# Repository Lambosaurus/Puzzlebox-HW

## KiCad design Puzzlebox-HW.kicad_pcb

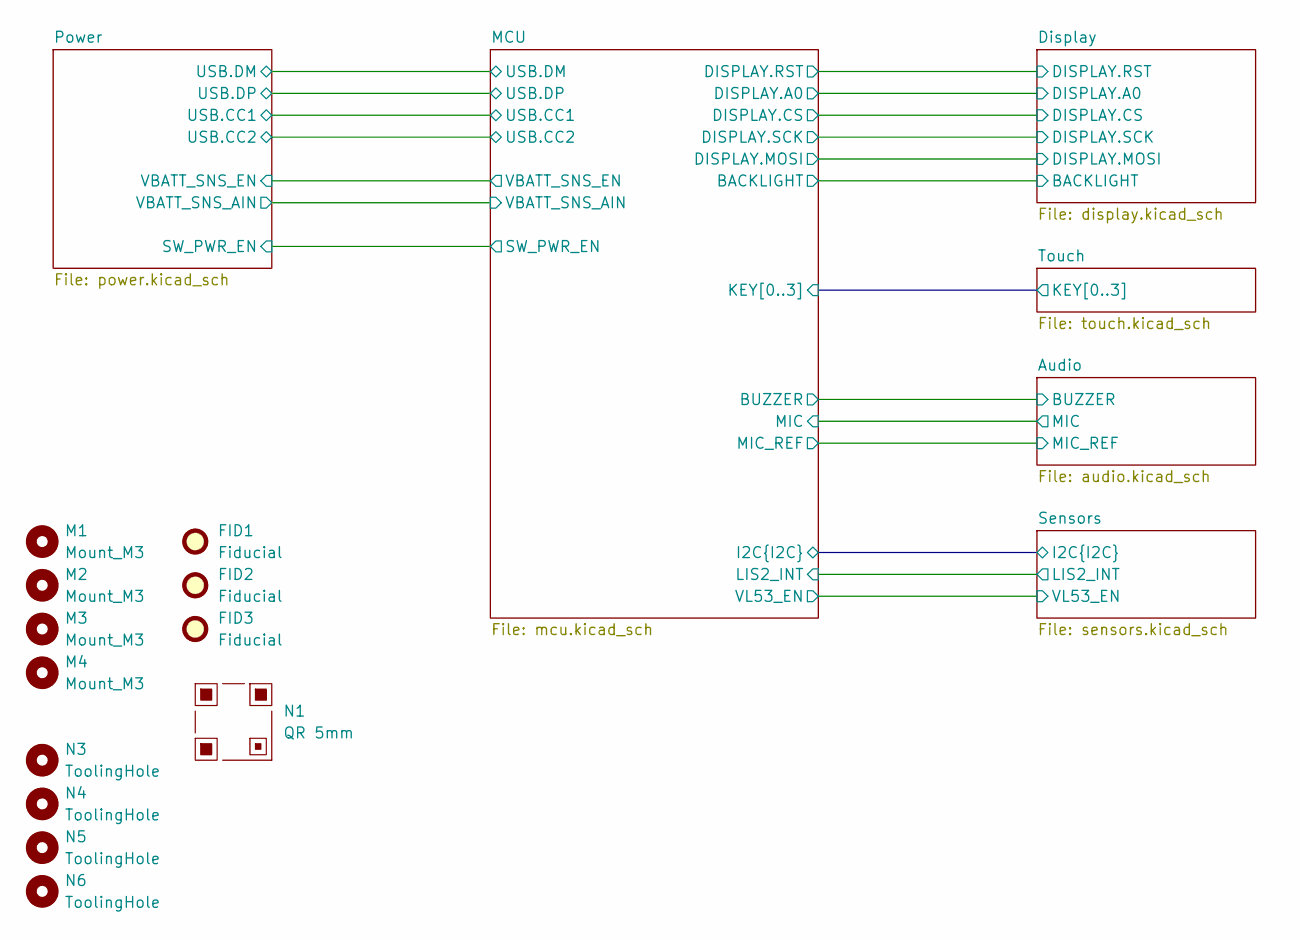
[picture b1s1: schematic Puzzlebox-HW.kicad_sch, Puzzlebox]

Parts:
FID1, FID2, FID3: Fiducial; Fiducial_2mm
M1, M2, M3, M4: Mount_M3
N1: QR 5mm; QR_5mm_JLC
N3, N4, N5, N6: ToolingHole; ToolingHole_1mm

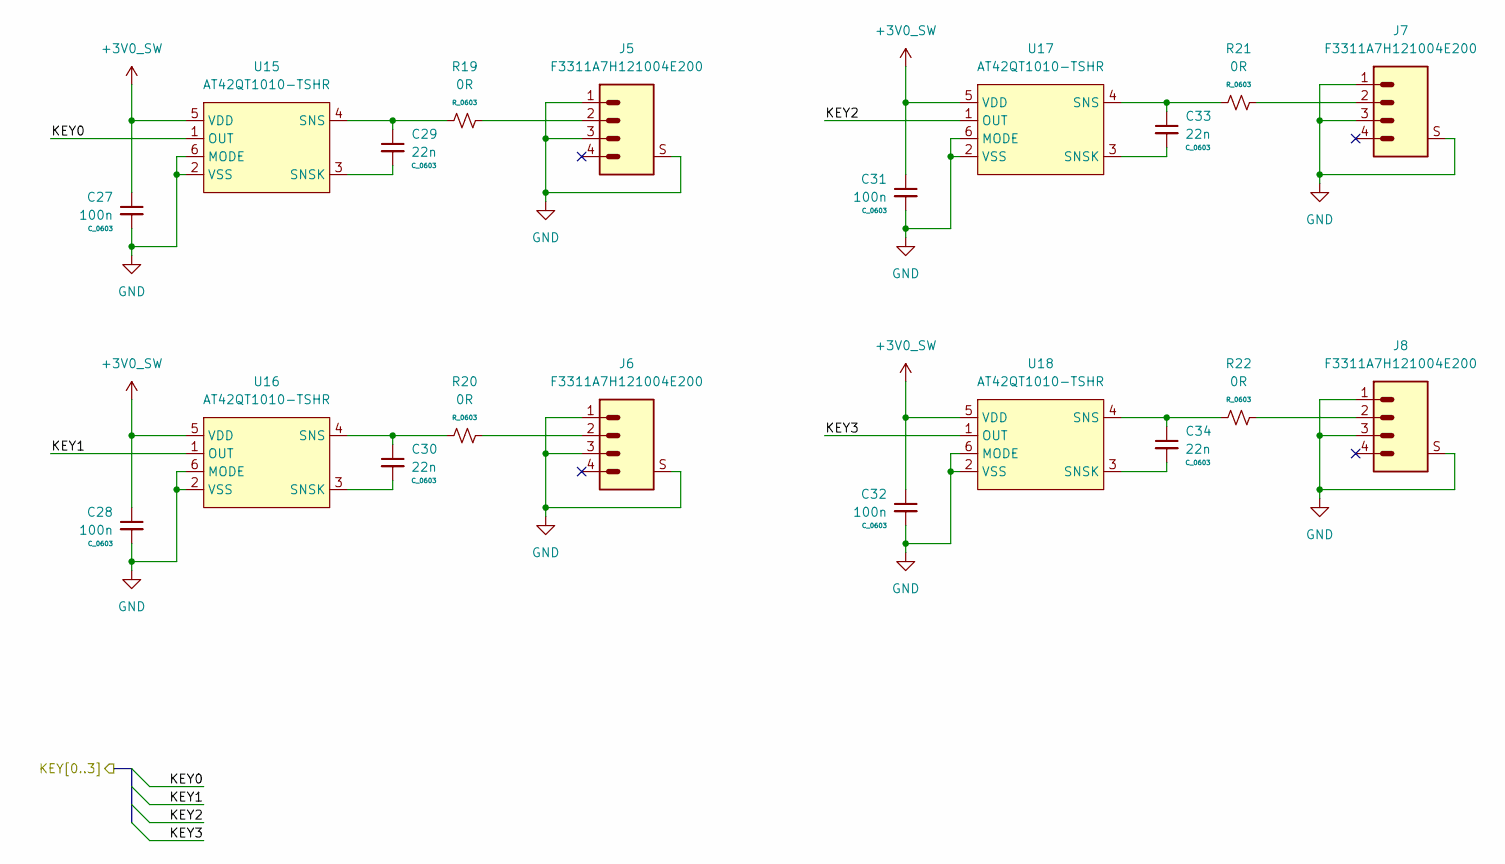
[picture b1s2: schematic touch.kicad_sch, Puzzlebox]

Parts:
C27, C28, C31, C32: 100n; C_0603
C29, C30, C33, C34: 22n; C_0603
J5, J6, J7, J8: F3311A7H121004E200
R19, R20, R21, R22: 0R; R_0603
U15, U16, U17, U18: AT42QT1010-TSHR; SOT23_6

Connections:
+3V0_SW: C27.1, C28.1, C31.1, C32.1, U15.5 (VDD), U16.5 (VDD), U17.5 (VDD), U18.5 (VDD); also elsewhere on the board
/MCU/KEY0: U15.1 (OUT); also elsewhere on the board
/MCU/KEY1: U16.1 (OUT); also elsewhere on the board
/MCU/KEY2: U17.1 (OUT); also elsewhere on the board
/MCU/KEY3: U18.1 (OUT); also elsewhere on the board
GND: C27.2, C28.2, C31.2, C32.2, J5.1, J5.3, J5.S, J6.1, J6.3, J6.S, J7.1, J7.3, J7.S, J8.1, J8.3, J8.S, U15.2 (VSS), U15.6 (MODE), U16.2 (VSS), U16.6 (MODE), U17.2 (VSS), U17.6 (MODE), U18.2 (VSS), U18.6 (MODE); also elsewhere on the board
unnamed: J5.2, R19.2
unnamed: J6.2, R20.2
unnamed: J7.2, R21.2
unnamed: J8.2, R22.2
unnamed: C29.1, R19.1, U15.4 (SNS)
unnamed: C29.2, U15.3 (SNSK)
unnamed: C30.1, R20.1, U16.4 (SNS)
unnamed: C30.2, U16.3 (SNSK)
unnamed: C33.1, R21.1, U17.4 (SNS)
unnamed: C33.2, U17.3 (SNSK)
unnamed: C34.1, R22.1, U18.4 (SNS)
unnamed: C34.2, U18.3 (SNSK)

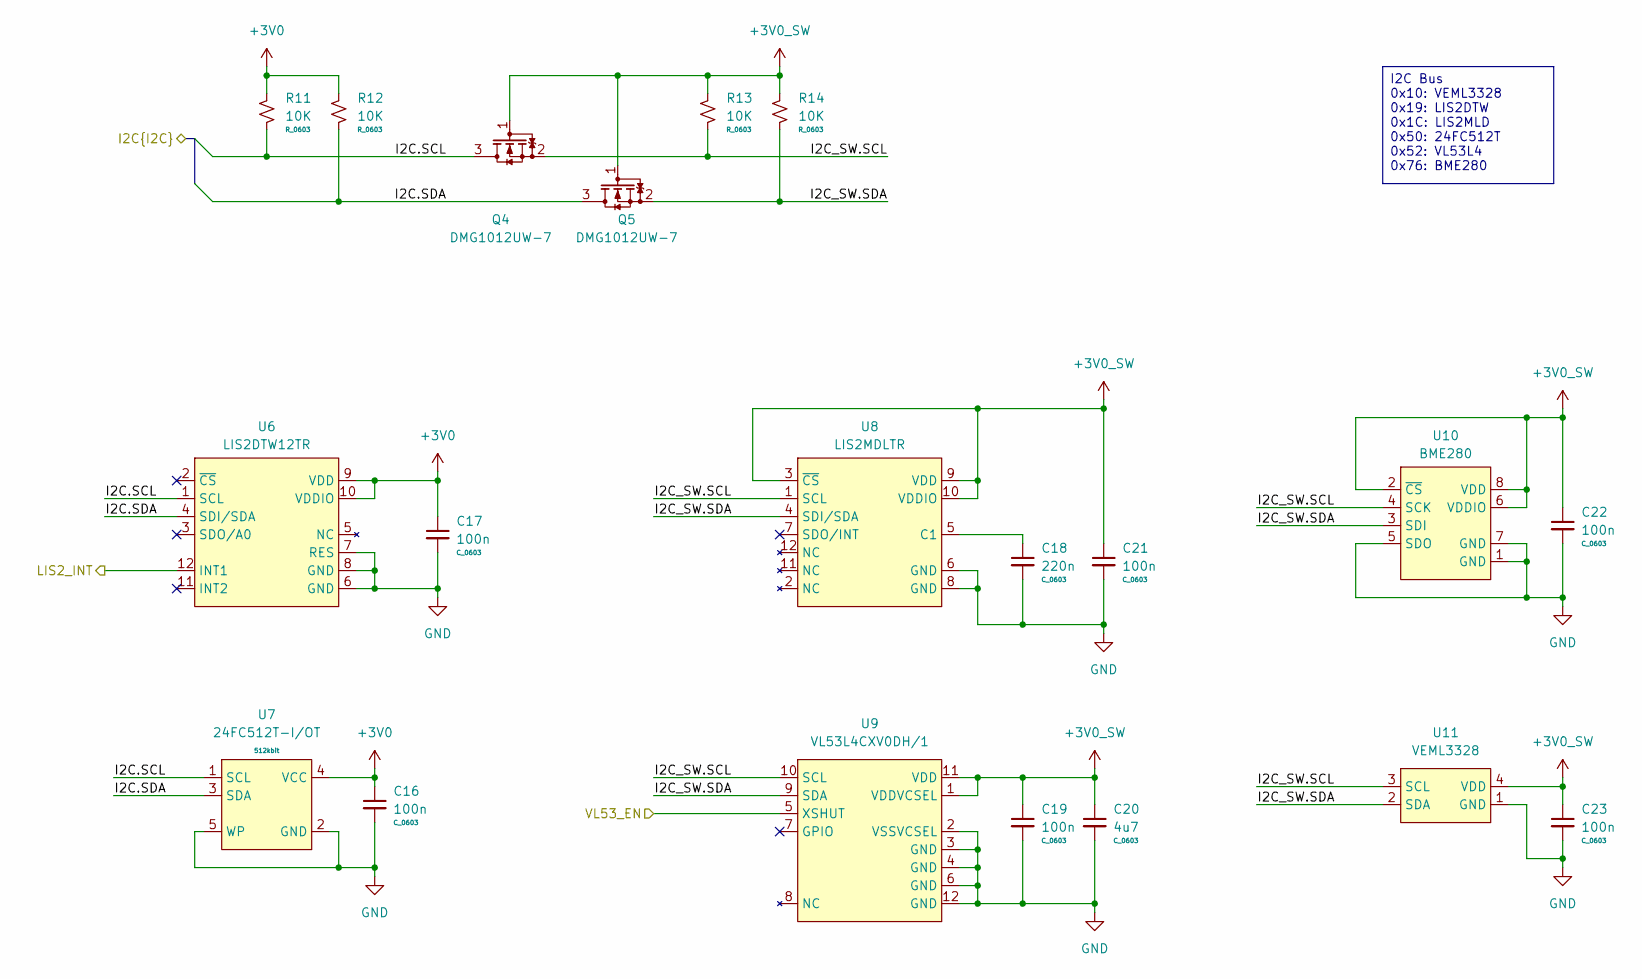
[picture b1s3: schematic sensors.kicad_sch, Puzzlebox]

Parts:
C16, C17, C19, C21, C22, C23: 100n; C_0603
C18: 220n; C_0603
C20: 4u7; C_0603
Q4, Q5: DMG1012UW-7; SC70-3
R11, R12, R13, R14: 10K; R_0603
U6: LIS2DTW12TR; LGA12_05_2x2_ST
U7: 24FC512T-I/OT; SOT23_5
U8: LIS2MDLTR; LGA12_05_2x2_ST
U9: VL53L4CXV0DH/1; ST_VL53Lxx
U10: BME280; LGA8_025_2.5x1_Bosch
U11: VEML3328; Vishay_80216OPLGA4L

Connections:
+3V0: C16.1, C17.1, R11.1, R12.1, U6.9 (VDD), U6.10 (VDDIO), U7.4 (VCC); also elsewhere on the board
+3V0_SW: C19.1, C20.1, C21.1, C22.1, C23.1, Q4.1 (G), Q5.1 (G), R13.1, R14.1, U8.3 (~CS), U8.9 (VDD), U8.10 (VDDIO), U9.1 (VDDVCSEL), U9.11 (VDD), U10.2 (~CS), U10.6 (VDDIO), U10.8 (VDD), U11.4 (VDD); also elsewhere on the board
/MCU/I2C.SCL: Q4.3 (D), R11.2, U6.1 (SCL), U7.1 (SCL); also elsewhere on the board
/MCU/I2C.SDA: Q5.3 (D), R12.2, U6.4 (SDI/SDA), U7.3 (SDA); also elsewhere on the board
/MCU/LIS2_INT: U6.12 (INT1); also elsewhere on the board
/MCU/VL53_EN: U9.5 (XSHUT); also elsewhere on the board
/Sensors/I2C_SW.SCL: Q4.2 (S), R13.2, U8.1 (SCL), U9.10 (SCL), U10.4 (SCK), U11.3 (SCL)
/Sensors/I2C_SW.SDA: Q5.2 (S), R14.2, U8.4 (SDI/SDA), U9.9 (SDA), U10.3 (SDI), U11.2 (SDA)
GND: C16.2, C17.2, C18.2, C19.2, C20.2, C21.2, C22.2, C23.2, U6.6 (GND), U6.7 (RES), U6.8 (GND), U7.2 (GND), U7.5 (WP), U8.6 (GND), U8.8 (GND), U9.2 (VSSVCSEL), U9.3 (GND), U9.4 (GND), U9.6 (GND), U9.12 (GND), U10.1 (GND), U10.5 (SDO), U10.7 (GND), U11.1 (GND); also elsewhere on the board
unnamed: C18.1, U8.5 (C1)

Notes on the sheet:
I2C Bus 0x10: VEML3328 0x19: LIS2DTW 0x1C: LIS2MLD 0x50: 24FC512T 0x52: VL53L4 0x76: BME280

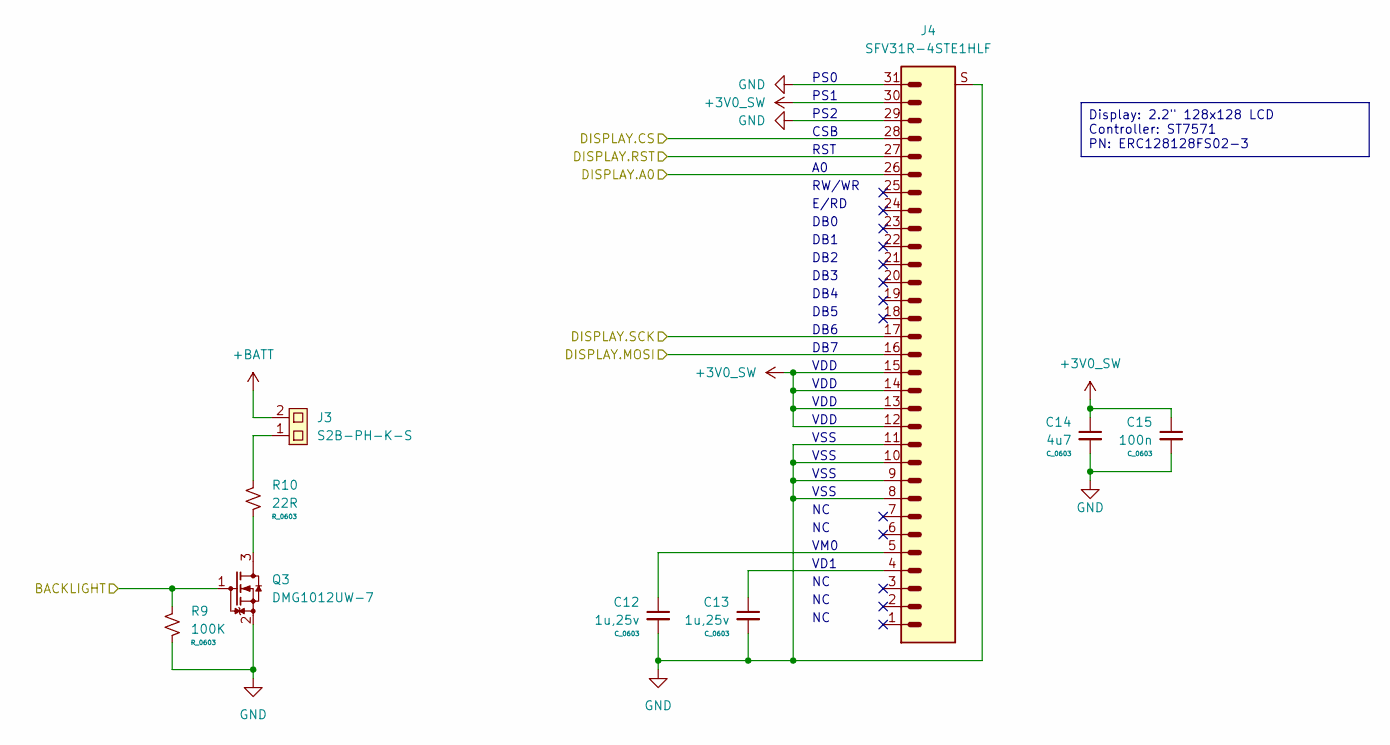
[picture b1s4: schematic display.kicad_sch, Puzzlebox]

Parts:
C12, C13: 1u,25v; C_0603
C14: 4u7; C_0603
C15: 100n; C_0603
J3: S2B-PH-K-S; JST-S2B-PH-K-S
J4: SFV31R-4STE1HLF
Q3: DMG1012UW-7; SC70-3
R9: 100K; R_0603
R10: 22R; R_0603

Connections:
+3V0_SW: C14.1, C15.1, J4.12, J4.13, J4.14, J4.15, J4.30; also elsewhere on the board
+BATT: J3.2; also elsewhere on the board
/Display/BACKLIGHT: Q3.1 (G), R9.1; also elsewhere on the board
/Display/DISPLAY.A0: J4.26; also elsewhere on the board
/Display/DISPLAY.CS: J4.28; also elsewhere on the board
/Display/DISPLAY.MOSI: J4.16; also elsewhere on the board
/Display/DISPLAY.RST: J4.27; also elsewhere on the board
/Display/DISPLAY.SCK: J4.17; also elsewhere on the board
GND: C12.2, C13.2, C14.2, C15.2, J4.8, J4.9, J4.10, J4.11, J4.29, J4.31, J4.S, Q3.2 (S), R9.2; also elsewhere on the board
unnamed: C12.1, J4.5
unnamed: C13.1, J4.4
unnamed: J3.1, R10.1
unnamed: Q3.3 (D), R10.2

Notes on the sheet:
PS0
E/RD
VSS
PS2
VM0
VD1
DB4
DB7
RST
DB6
RW/WR
PS1
DB0
VDD
DB1
DB3
DB2
DB5
CSB
Display: 2.2" 128x128 LCD Controller: ST7571 PN: ERC128128FS02-3

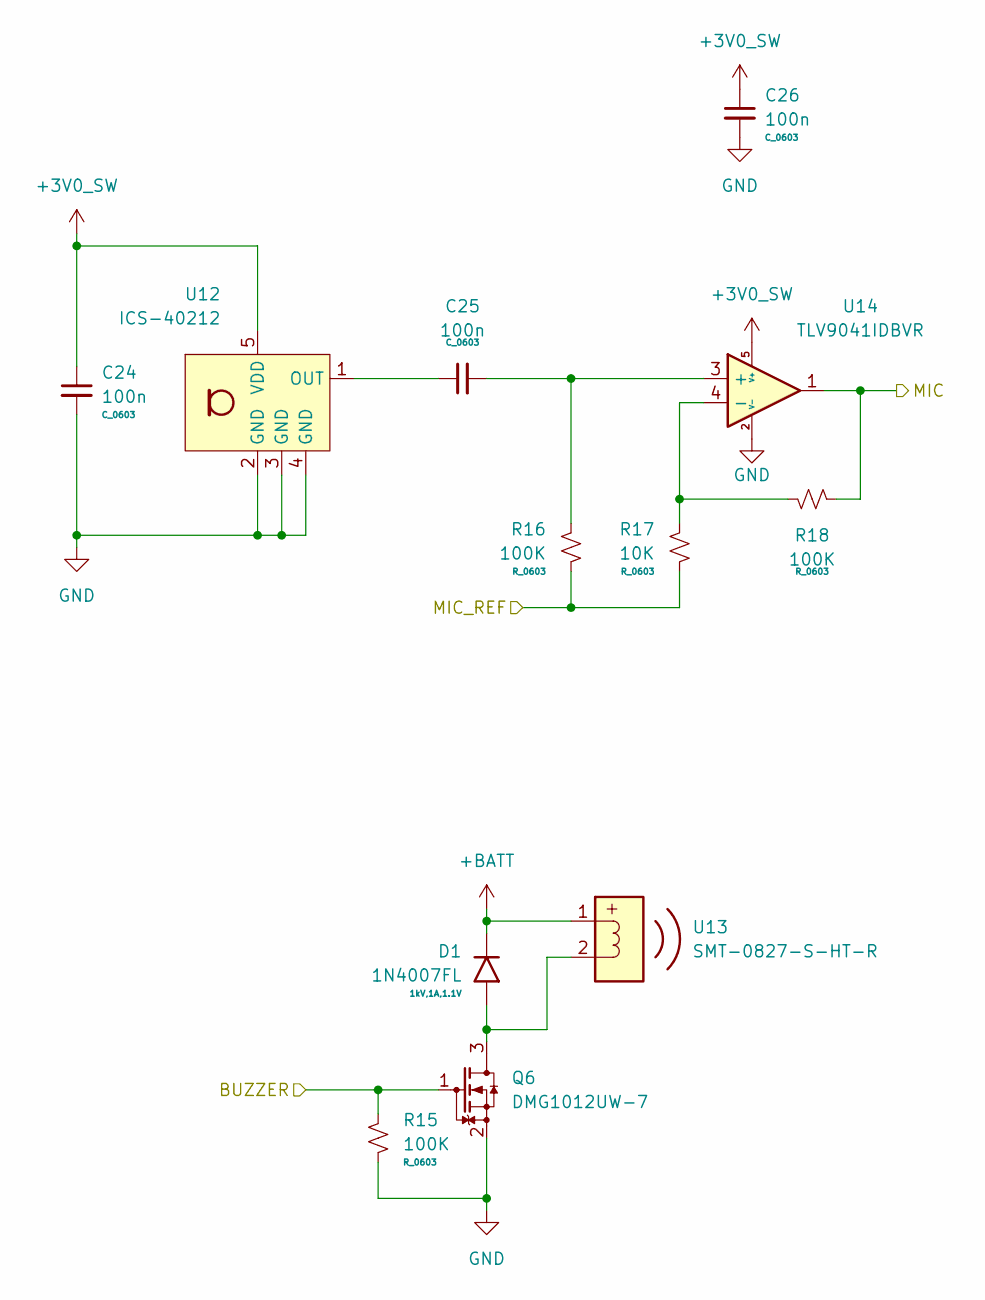
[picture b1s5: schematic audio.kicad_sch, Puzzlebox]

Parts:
C24, C25, C26: 100n; C_0603
D1: 1N4007FL; D_SOD_123
Q6: DMG1012UW-7; SC70-3
R15, R16, R18: 100K; R_0603
R17: 10K; R_0603
U12: ICS-40212
U13: SMT-0827-S-HT-R; SMT_0827_S_HT_R
U14: TLV9041IDBVR; SOT23_5

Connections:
+3V0_SW: C24.1, C26.1, U12.5 (VDD), U14.5 (V+); also elsewhere on the board
+BATT: D1.1, U13.1; also elsewhere on the board
/Audio/BUZZER: Q6.1 (G), R15.1; also elsewhere on the board
/Audio/MIC: R18.2, U14.1; also elsewhere on the board
/Audio/MIC_REF: R16.2, R17.1; also elsewhere on the board
GND: C24.2, C26.2, Q6.2 (S), R15.2, U12.2 (GND), U12.3 (GND), U12.4 (GND), U14.2 (V-); also elsewhere on the board
unnamed: D1.2, Q6.3 (D), U13.2
unnamed: C25.1, U12.1 (OUT)
unnamed: C25.2, R16.1, U14.3 (+)
unnamed: R17.2, R18.1, U14.4 (-)

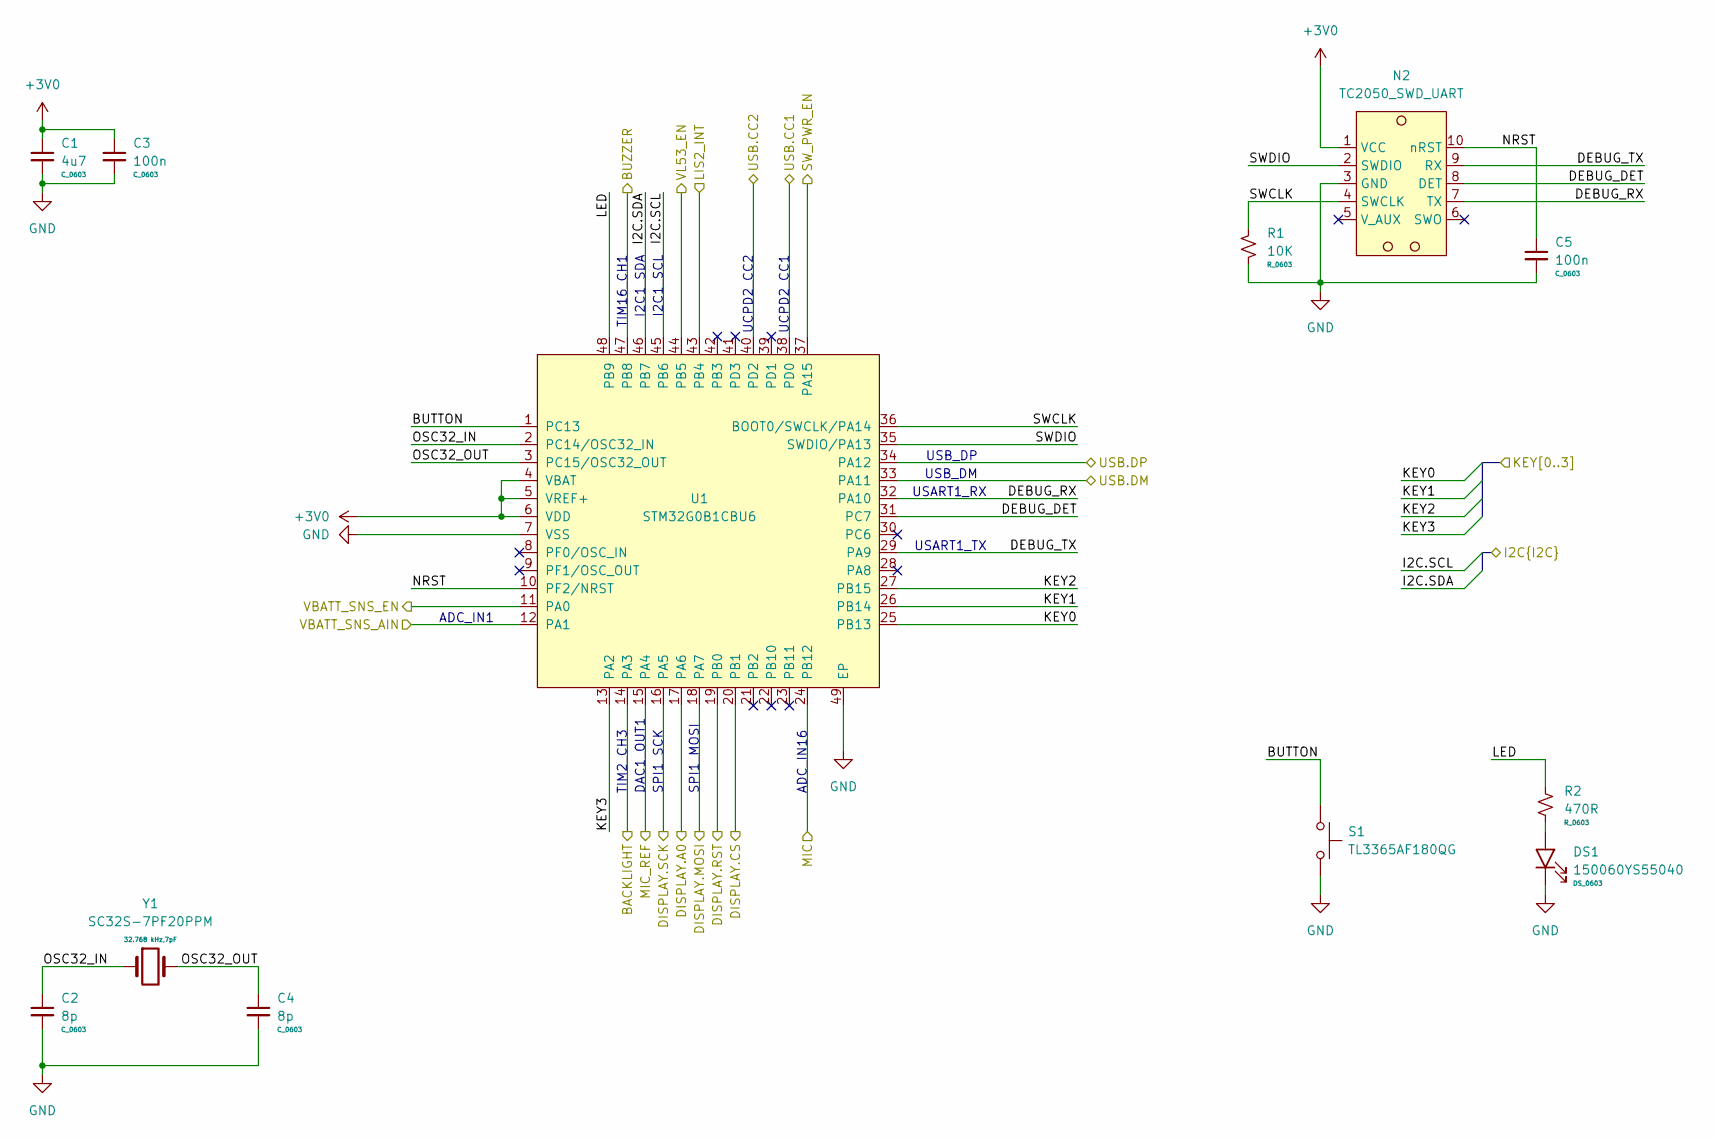
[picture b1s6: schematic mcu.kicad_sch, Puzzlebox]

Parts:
C1: 4u7; C_0603
C2, C4: 8p; C_0603
C3, C5: 100n; C_0603
DS1: 150060YS55040; DS_0603
N2: TC2050_SWD_UART; TagConnect_TC2050
R1: 10K; R_0603
R2: 470R; R_0603
S1: TL3365AF180QG; Button_4.2x3.2
U1: STM32G0B1CBU6; QFN48_05_7x7_EP
Y1: SC32S-7PF20PPM; Crystal_SMD2_3.2x1.5

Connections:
+3V0: C1.1, C3.1, N2.1 (VCC), U1.4 (VBAT), U1.5 (VREF+), U1.6 (VDD); also elsewhere on the board
/Audio/BUZZER: U1.47 (PB8); also elsewhere on the board
/Audio/MIC: U1.24 (PB12); also elsewhere on the board
/Audio/MIC_REF: U1.15 (PA4); also elsewhere on the board
/Display/BACKLIGHT: U1.14 (PA3); also elsewhere on the board
/Display/DISPLAY.A0: U1.17 (PA6); also elsewhere on the board
/Display/DISPLAY.CS: U1.20 (PB1); also elsewhere on the board
/Display/DISPLAY.MOSI: U1.18 (PA7); also elsewhere on the board
/Display/DISPLAY.RST: U1.19 (PB0); also elsewhere on the board
/Display/DISPLAY.SCK: U1.16 (PA5); also elsewhere on the board
/MCU/BUTTON: S1.1, U1.1 (PC13)
/MCU/DEBUG_DET: N2.8 (DET), U1.31 (PC7)
/MCU/DEBUG_RX: N2.7 (TX), U1.32 (PA10)
/MCU/DEBUG_TX: N2.9 (RX), U1.29 (PA9)
/MCU/I2C.SCL: U1.45 (PB6); also elsewhere on the board
/MCU/I2C.SDA: U1.46 (PB7); also elsewhere on the board
/MCU/KEY0: U1.25 (PB13); also elsewhere on the board
/MCU/KEY1: U1.26 (PB14); also elsewhere on the board
/MCU/KEY2: U1.27 (PB15); also elsewhere on the board
/MCU/KEY3: U1.13 (PA2); also elsewhere on the board
/MCU/LED: R2.1, U1.48 (PB9)
/MCU/LIS2_INT: U1.43 (PB4); also elsewhere on the board
/MCU/NRST: C5.1, N2.10 (nRST), U1.10 (PF2/NRST)
/MCU/OSC32_IN: C2.1, U1.2 (PC14/OSC32_IN), Y1.1
/MCU/OSC32_OUT: C4.1, U1.3 (PC15/OSC32_OUT), Y1.2
/MCU/SWCLK: N2.4 (SWCLK), R1.1, U1.36 (BOOT0/SWCLK/PA14)
/MCU/SWDIO: N2.2 (SWDIO), U1.35 (SWDIO/PA13)
/MCU/SW_PWR_EN: U1.37 (PA15); also elsewhere on the board
/MCU/USB.CC1: U1.38 (PD0); also elsewhere on the board
/MCU/USB.CC2: U1.40 (PD2); also elsewhere on the board
/MCU/USB.DM: U1.33 (PA11); also elsewhere on the board
/MCU/USB.DP: U1.34 (PA12); also elsewhere on the board
/MCU/VBATT_SNS_AIN: U1.12 (PA1); also elsewhere on the board
/MCU/VBATT_SNS_EN: U1.11 (PA0); also elsewhere on the board
/MCU/VL53_EN: U1.44 (PB5); also elsewhere on the board
GND: C1.2, C2.2, C3.2, C4.2, C5.2, DS1.1 (K), N2.3 (GND), R1.2, S1.2, U1.7 (VSS), U1.49 (EP); also elsewhere on the board
unnamed: DS1.2 (A), R2.2

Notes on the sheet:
UCPD2_CC1
SPI1_SCK
USB_DM
SPI1_MOSI
TIM16_CH1
UCPD2_CC2
ADC_IN1
USB_DP
DAC1_OUT1
TIM2_CH3
I2C1_SDA
I2C1_SCL
USART1_TX
USART1_RX
ADC_IN16

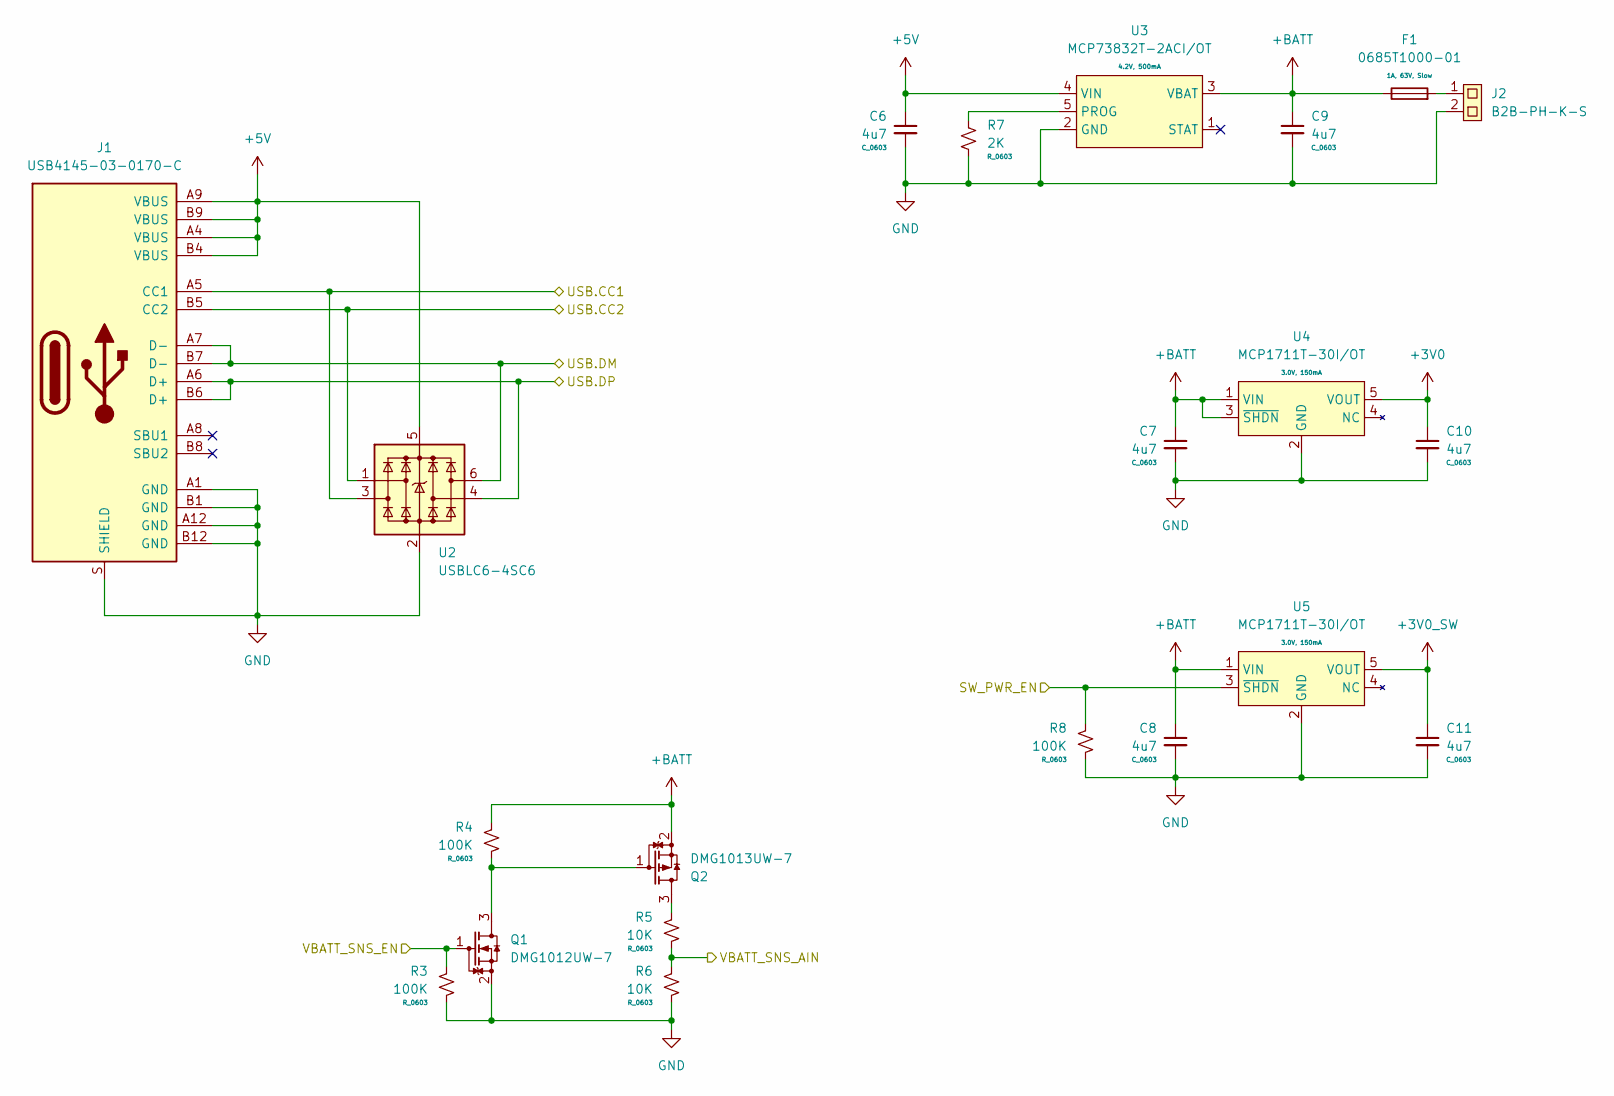
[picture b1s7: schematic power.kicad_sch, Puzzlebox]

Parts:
C6, C7, C8, C9, C10, C11: 4u7; C_0603
F1: 0685T1000-01; F_1206
J1: USB4145-03-0170-C; USB_C_USB4145-03-0170-C
J2: B2B-PH-K-S; JST_B2B-PH-K
Q1: DMG1012UW-7; SC70-3
Q2: DMG1013UW-7; SC70-3
R3, R4, R8: 100K; R_0603
R5, R6: 10K; R_0603
R7: 2K; R_0603
U2: USBLC6-4SC6; SOT23_6
U3: MCP73832T-2ACI/OT; SOT23_5
U4, U5: MCP1711T-30I/OT; SOT23_5

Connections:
+3V0: C10.1, U4.5 (VOUT); also elsewhere on the board
+3V0_SW: C11.1, U5.5 (VOUT); also elsewhere on the board
+5V: C6.1, J1.A4 (VBUS), J1.A9 (VBUS), J1.B4 (VBUS), J1.B9 (VBUS), U2.5, U3.4 (VIN)
+BATT: C7.1, C8.1, C9.1, F1.1, Q2.2 (S), R4.2, U3.3 (VBAT), U4.1 (VIN), U4.3 (~SHDN), U5.1 (VIN); also elsewhere on the board
/MCU/SW_PWR_EN: R8.2, U5.3 (~SHDN); also elsewhere on the board
/MCU/USB.CC1: J1.A5 (CC1), U2.3; also elsewhere on the board
/MCU/USB.CC2: J1.B5 (CC2), U2.1; also elsewhere on the board
/MCU/USB.DM: J1.A7 (D-), J1.B7 (D-), U2.6; also elsewhere on the board
/MCU/USB.DP: J1.A6 (D+), J1.B6 (D+), U2.4; also elsewhere on the board
/MCU/VBATT_SNS_AIN: R5.1, R6.2; also elsewhere on the board
/MCU/VBATT_SNS_EN: Q1.1 (G), R3.2; also elsewhere on the board
GND: C6.2, C7.2, C8.2, C9.2, C10.2, C11.2, J1.A1 (GND), J1.A12 (GND), J1.B1 (GND), J1.B12 (GND), J1.S (SHIELD), J2.2, Q1.2 (S), R3.1, R6.1, R7.2, R8.1, U2.2, U3.2 (GND), U4.2 (GND), U5.2 (GND); also elsewhere on the board
unnamed: F1.2, J2.1
unnamed: Q1.3 (D), Q2.1 (G), R4.1
unnamed: Q2.3 (D), R5.2
unnamed: R7.1, U3.5 (PROG)

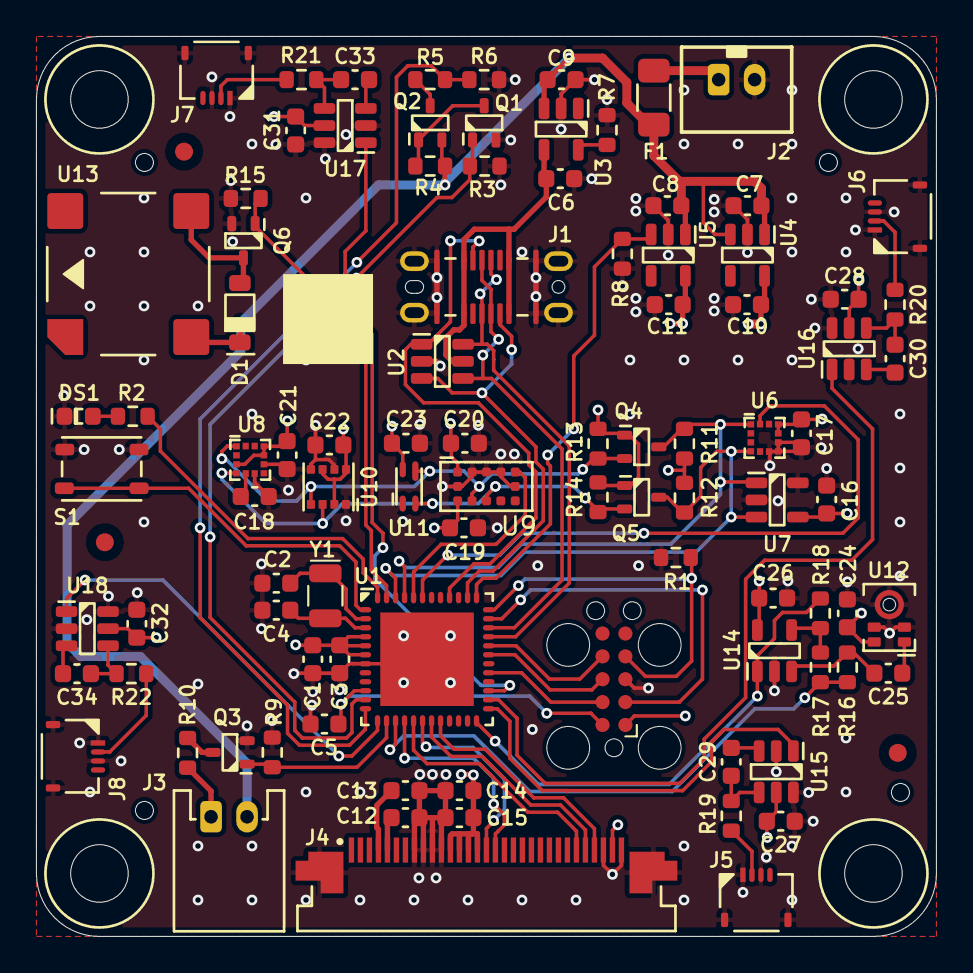
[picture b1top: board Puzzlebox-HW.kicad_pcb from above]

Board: 4 copper layers, 50.0 x 50.0 mm, 106 parts (0 on the bottom side), 67 nets.

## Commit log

2025-12-27 Initial schematics
2025-12-27 Initial layout
2025-12-28 Add some notes. Configure outputs.
2025-12-28 Move project into subdir
2025-12-28 Add touch key
2025-12-29 Use layer names
